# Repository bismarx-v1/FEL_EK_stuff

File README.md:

# Repo description
This repo is used for storing study materials, homework, books, scripts and projects that are used for studying at CTU FEE

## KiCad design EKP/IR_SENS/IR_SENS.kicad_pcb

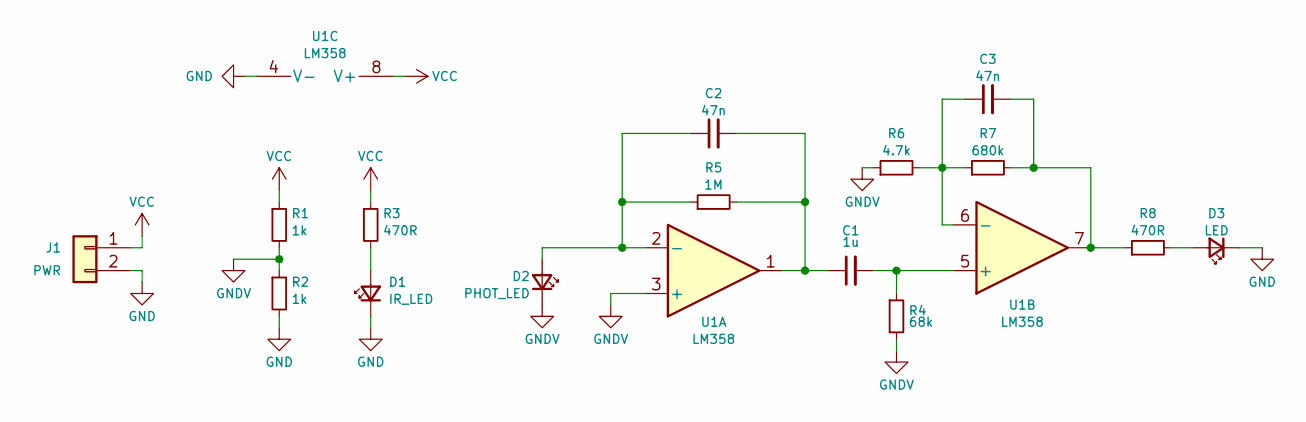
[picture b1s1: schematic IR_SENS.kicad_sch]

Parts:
C1: 1u; C_Disc_D5.0mm_W2.5mm_P5.00mm
C2, C3: 47n; C_Disc_D5.0mm_W2.5mm_P5.00mm
D1: IR_LED; LED_D5.0mm
D2: PHOT_LED; LED_D5.0mm
D3: LED; LED_D5.0mm
J1: PWR; PinHeader_1x02_P2.54mm_Vertical
R1, R2: 1k; R_Axial_DIN0207_L6.3mm_D2.5mm_P10.16mm_Horizontal
R3, R8: 470R; R_Axial_DIN0207_L6.3mm_D2.5mm_P10.16mm_Horizontal
R4: 68k; R_Axial_DIN0207_L6.3mm_D2.5mm_P10.16mm_Horizontal
R5: 1M; R_Axial_DIN0207_L6.3mm_D2.5mm_P10.16mm_Horizontal
R6: 4.7k; R_Axial_DIN0207_L6.3mm_D2.5mm_P10.16mm_Horizontal
R7: 680k; R_Axial_DIN0207_L6.3mm_D2.5mm_P10.16mm_Horizontal
U1: LM358; DIP-8_W7.62mm_LongPads

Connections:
GND: D1.1 (K), D3.1 (K), J1.2, R2.2, U1.4 (V-)
GNDV: D2.1 (K), R1.2, R2.1, R4.2, R6.1, U1.3 (+)
unnamed: C1.1, C2.2, R5.2, U1.1
unnamed: C3.2, R7.2, R8.1, U1.7
unnamed: D1.2 (A), R3.2
unnamed: C2.1, D2.2 (A), R5.1, U1.2 (-)
unnamed: D3.2 (A), R8.2
unnamed: C1.2, R4.1, U1.5 (+)
unnamed: C3.1, R6.2, R7.1, U1.6 (-)
VCC: J1.1, R1.1, R3.1, U1.8 (V+)

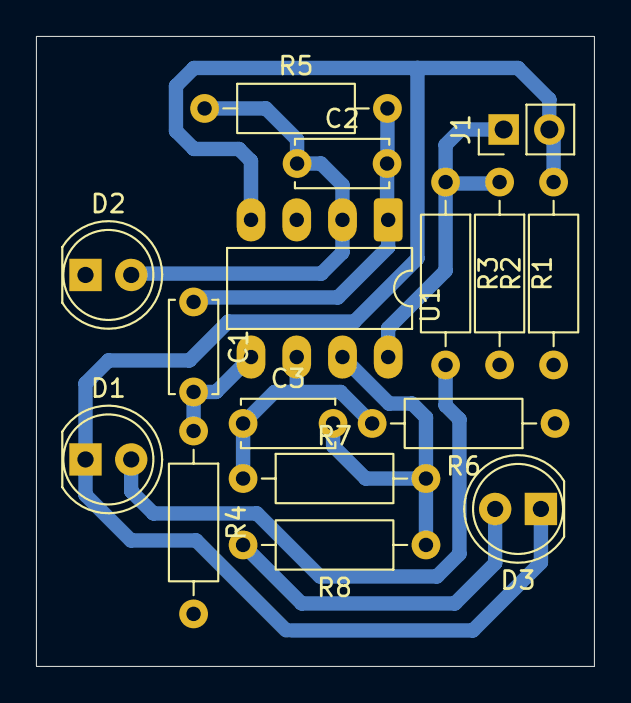
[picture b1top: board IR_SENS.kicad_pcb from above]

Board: 2 copper layers, 31.0 x 35.0 mm, 16 parts (0 on the bottom side), 10 nets.

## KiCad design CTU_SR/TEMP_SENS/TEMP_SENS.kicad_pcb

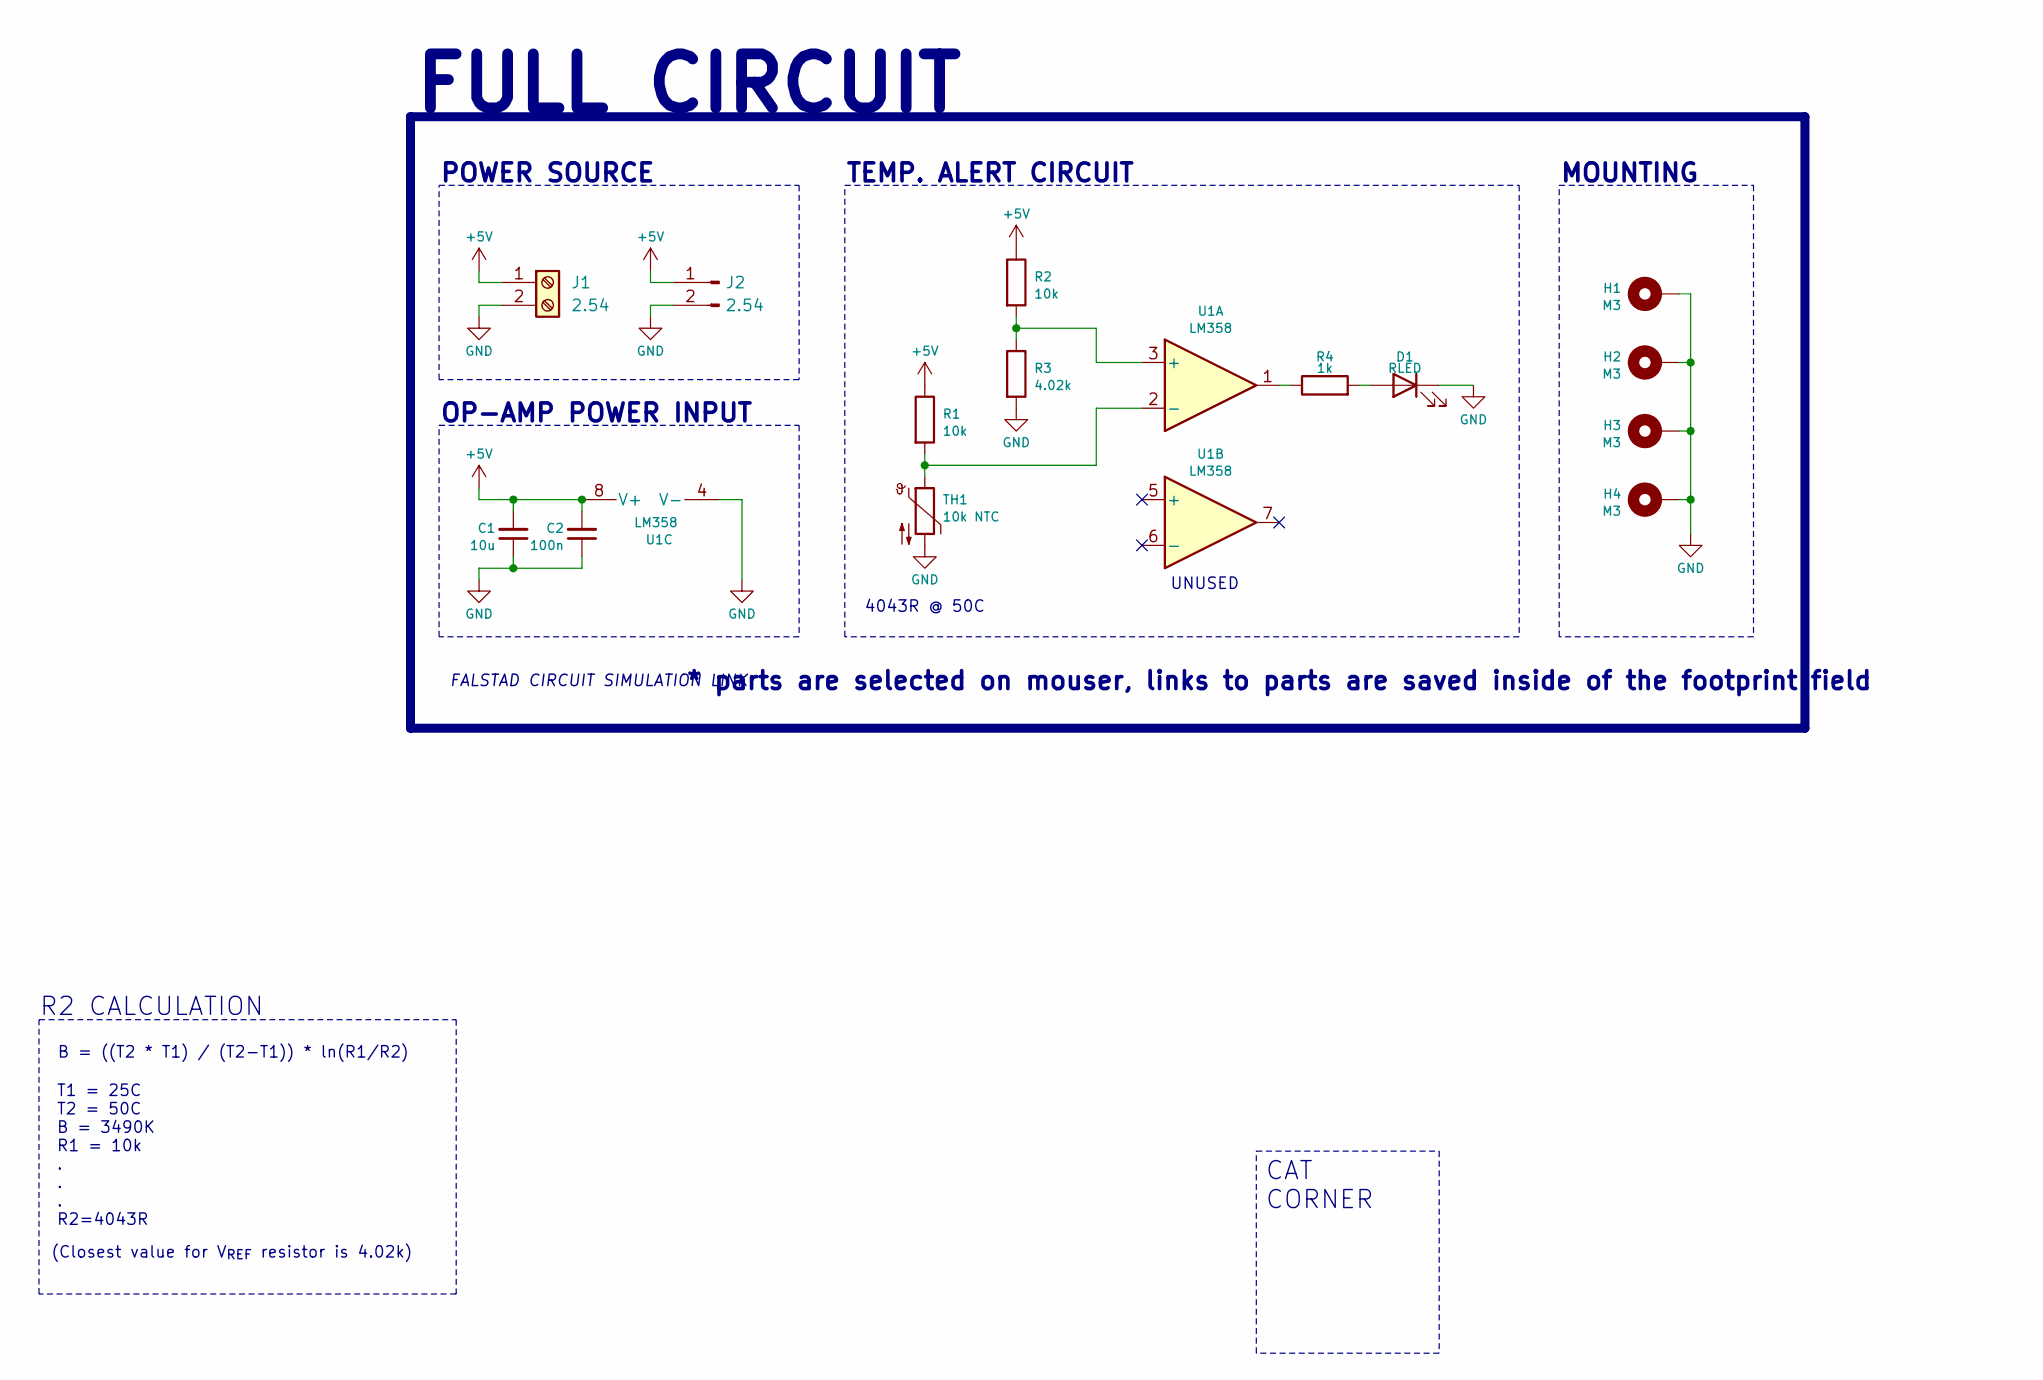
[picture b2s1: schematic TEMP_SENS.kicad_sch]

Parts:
C1: 10u; C_0805_2012Metric
C2: 100n; C_0805_2012Metric
D1: RLED; LED_0805_2012Metric
H1, H2, H3, H4: M3; MountingHole_3.2mm_M3_Pad_Via
J1: 2.54; TerminalBlock_TE_282834-2_1x02_P2.54mm_Horizontal
J2: 2.54; PinHeader_1x02_P2.54mm_Vertical
R1, R2: 10k; R_0805_2012Metric
R3: 4.02k; R_0805_2012Metric
R4: 1k; R_0805_2012Metric
TH1: 10k NTC; R_0402_1005Metric_Pad0.72x0.64mm_HandSolder
U1: LM358; SOT-23-8

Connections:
+5V: C1.2, C2.2, J1.1, J2.1, R1.1, R2.1, U1.8 (V+)
GND: C1.1, C2.1, D1.1 (K), H1.1 (1_1), H2.1 (1_1), H3.1 (1_1), H4.1 (1_1), J1.2, J2.2, R3.2, TH1.2, U1.4 (V-)
unnamed: D1.2 (A), R4.2
unnamed: R4.1, U1.1
unnamed: R2.2, R3.1, U1.3 (+)
unnamed: R1.2, TH1.1, U1.2 (-)

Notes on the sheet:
TEMP. ALERT CIRCUIT
POWER SOURCE
* parts are selected on mouser, links to parts are saved inside of the footprint field
UNUSED
FULL CIRCUIT
(Closest value for V_{REF} resistor is 4.02k)
FALSTAD CIRCUIT SIMULATION LINK
4043R @ 50C
OP-AMP POWER INPUT
MOUNTING
T1 = 25C T2 = 50C B = 3490K R1 = 10k . . . R2=4043R
B = ((T2 * T1) / (T2-T1)) * ln(R1/R2)
R2 CALCULATION
CAT CORNER

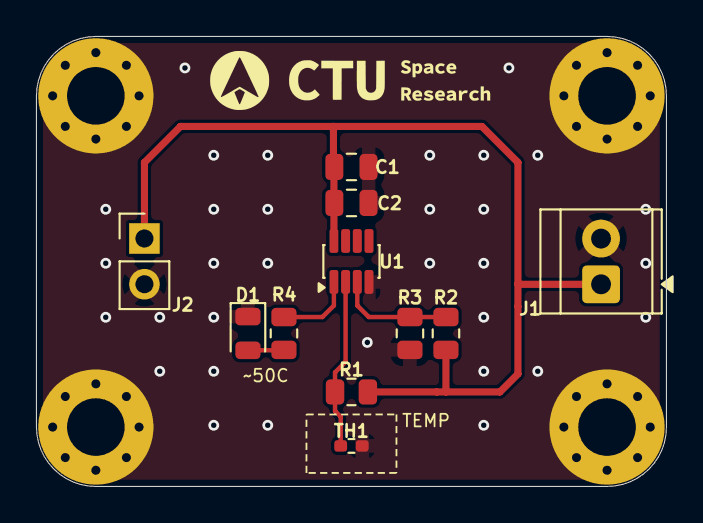
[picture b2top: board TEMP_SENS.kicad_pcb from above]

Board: 2 copper layers, 35.0 x 25.0 mm, 15 parts (0 on the bottom side), 6 nets.
